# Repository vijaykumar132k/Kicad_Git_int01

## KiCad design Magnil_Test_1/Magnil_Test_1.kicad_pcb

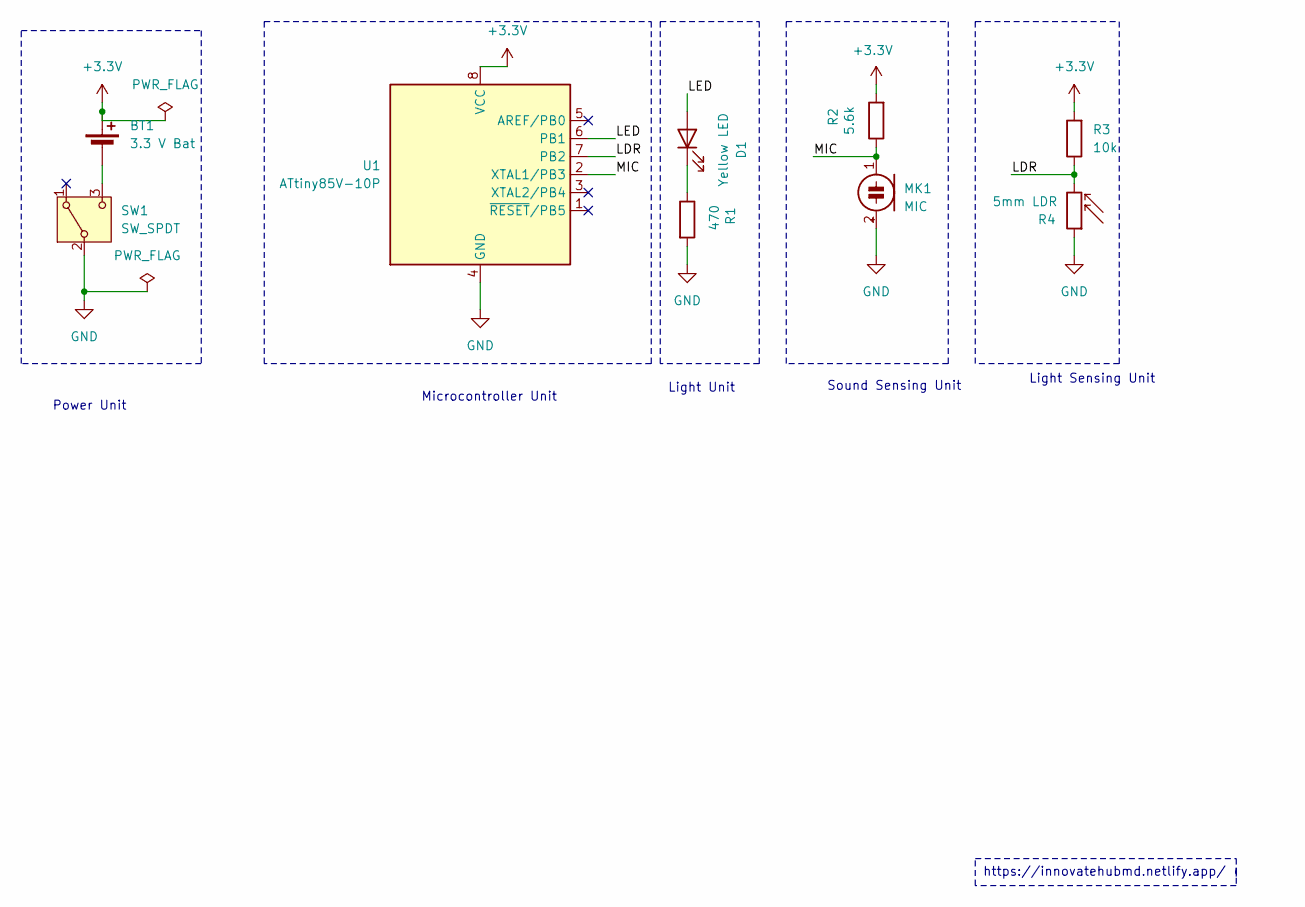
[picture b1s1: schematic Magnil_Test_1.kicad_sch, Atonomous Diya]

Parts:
BT1: 3.3 V Bat; BatteryHolder_ComfortableElectronic_CH273-2450_1x2450
D1: Yellow LED; LED_D5.0mm
MK1: MIC; PinHeader_1x02_P2.54mm_Vertical
R1: 470; R_Axial_DIN0207_L6.3mm_D2.5mm_P15.24mm_Horizontal
R2: 5.6k; R_Axial_DIN0207_L6.3mm_D2.5mm_P15.24mm_Horizontal
R3: 10k; R_Axial_DIN0207_L6.3mm_D2.5mm_P15.24mm_Horizontal
R4: 5mm LDR; R_LDR_10x8.5mm_P7.6mm_Vertical
SW1: SW_SPDT; SW_Slide_SPDT_Angled_CK_OS102011MA1Q
U1: ATtiny85V-10P; DIP-8_W7.62mm

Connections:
+3.3V: BT1.1 (+), R2.2, R3.2, U1.8 (VCC)
/LDR: R3.1, R4.2, U1.7 (PB2)
/LED: D1.2 (A), U1.6 (PB1)
/MIC: MK1.1 (-), R2.1, U1.2 (XTAL1/PB3)
GND: MK1.2 (+), R1.2, R4.1, SW1.2 (B), U1.4 (GND)
unnamed: BT1.2 (-), SW1.3 (C)
unnamed: D1.1 (K), R1.1

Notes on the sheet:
https://innovatehubmd.netlify.app/
Light Sensing Unit
Microcontroller Unit
Power Unit
Sound Sensing Unit
Light Unit

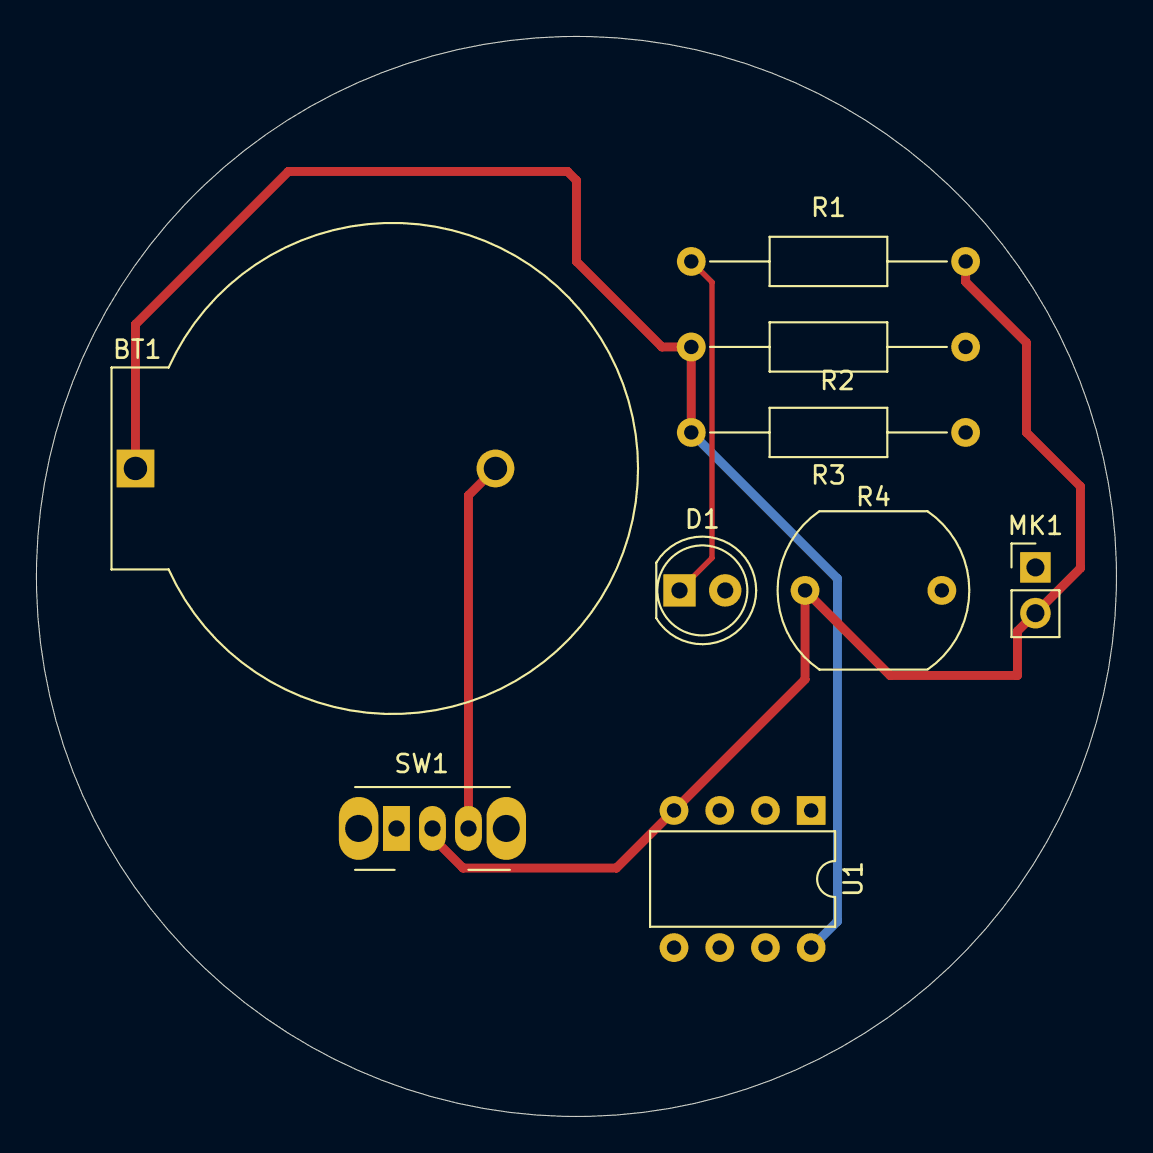
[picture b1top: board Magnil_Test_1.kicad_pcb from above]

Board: 2 copper layers, 60.0 x 60.0 mm, 9 parts (0 on the bottom side), 7 nets.

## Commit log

2024-04-01 Initial comment
2024-04-03 Battery name changed
2024-04-14 Routing stage one
2024-04-28 Wired resitor one
2024-04-28 test 28 4
